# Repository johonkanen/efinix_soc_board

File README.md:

# efinix_soc_board

Linux-capable control card for an AC in/out lab power supply, based on the **Efinix Titanium Ti135N484I3** FPGA. The
FPGA's hardened quad-core RISC-V runs Linux, with 1 GB LPDDR4, Gigabit Ethernet and eMMC. The card plugs into the
power supply baseboard ([ac_psu_kicad](https://github.com/johonkanen/ac_psu_kicad)) in place of the earlier Ti60F225
and Agilex 5 cards.

Status: schematic in progress. See **[STATUS.md](STATUS.md)** for where the work stands and what comes next.

| | |
|---|---|
| [MIGRATION_PLAN.md](MIGRATION_PLAN.md) | plan and decisions |
| [TI135_PCB_NOTES.md](TI135_PCB_NOTES.md) | Ti135 PCB design rules (banks, sequencing, configuration, LPDDR4) |
| [MECHANICAL.md](MECHANICAL.md) | outline and baseboard connector positions |
| [POWER_BUDGET.md](POWER_BUDGET.md) | power estimate and regulators |

The KiCad 10 project in `kicad/` is generated by scripts (`tools/build_schematic.sh`), using
[proteus2kicad](https://github.com/johonkanen/proteus2kicad) as a submodule in `tools/p2k`.

## Board

<!-- board-plots:start -->
<!-- Generated by kicad-board-plots; edits between these markers are overwritten. -->

3D renders and copper layers of `kicad/ti135_card.kicad_pcb`, the layers in stack order without silkscreen. Plotted by [kicad-board-plots](https://github.com/johonkanen/kicad-board-plots) on each board change; the images live on the `renders` branch.

<table>
<tr>
<td align="center"><br><b>3D, top</b></td>
<td align="center"><br><b>3D, bottom (seen from below)</b></td>
</tr>
<tr>
<td align="center"><br><b>F.Cu: signal (top)</b></td>
<td align="center"><br><b>In1.Cu: GND plane</b></td>
</tr>
<tr>
<td align="center"><br><b>In2.Cu: signal, phy_avdd33 pour</b></td>
<td align="center"><br><b>In3.Cu: 1V1, VCORE, 3V3, GND planes</b></td>
</tr>
<tr>
<td align="center"><br><b>In4.Cu: 1V8, 0V85 planes</b></td>
<td align="center"><br><b>In5.Cu: signal</b></td>
</tr>
<tr>
<td align="center"><br><b>In6.Cu: GND plane</b></td>
<td align="center"><br><b>B.Cu: signal, 1V1, GND, Net-(U201-SW), 5V0, 1V8 and 9 more pours (bottom, seen from the top)</b></td>
</tr>
</table>

<!-- board-plots:end -->

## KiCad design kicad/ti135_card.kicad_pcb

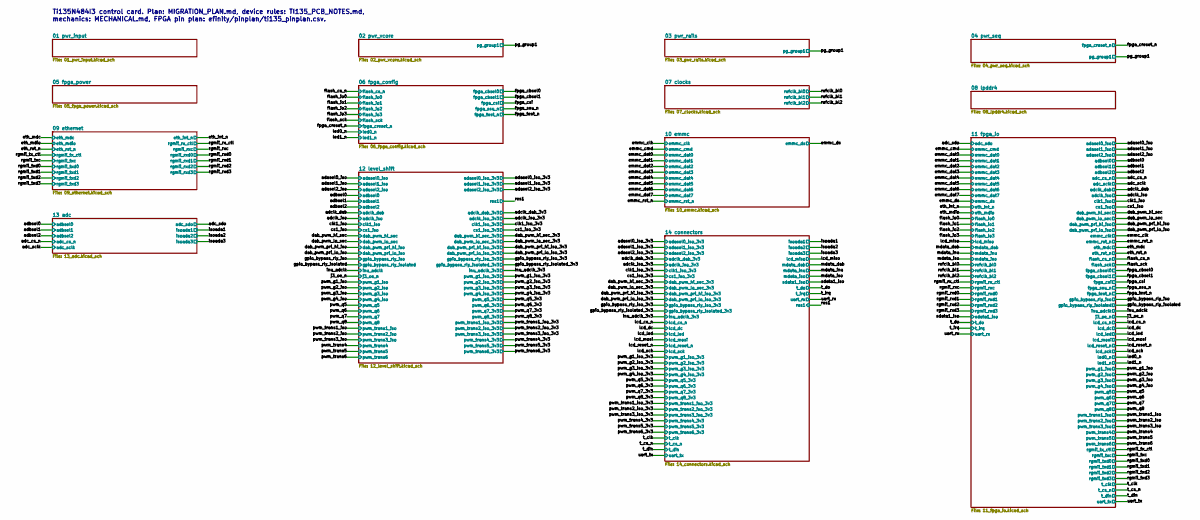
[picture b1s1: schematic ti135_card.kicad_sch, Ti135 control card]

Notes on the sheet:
Ti135N484I3 control card. Plan: MIGRATION_PLAN.md, device rules: TI135_PCB_NOTES.md, mechanics: MECHANICAL.md, FPGA pin plan: efinity/pinplan/ti135_pinplan.csv.

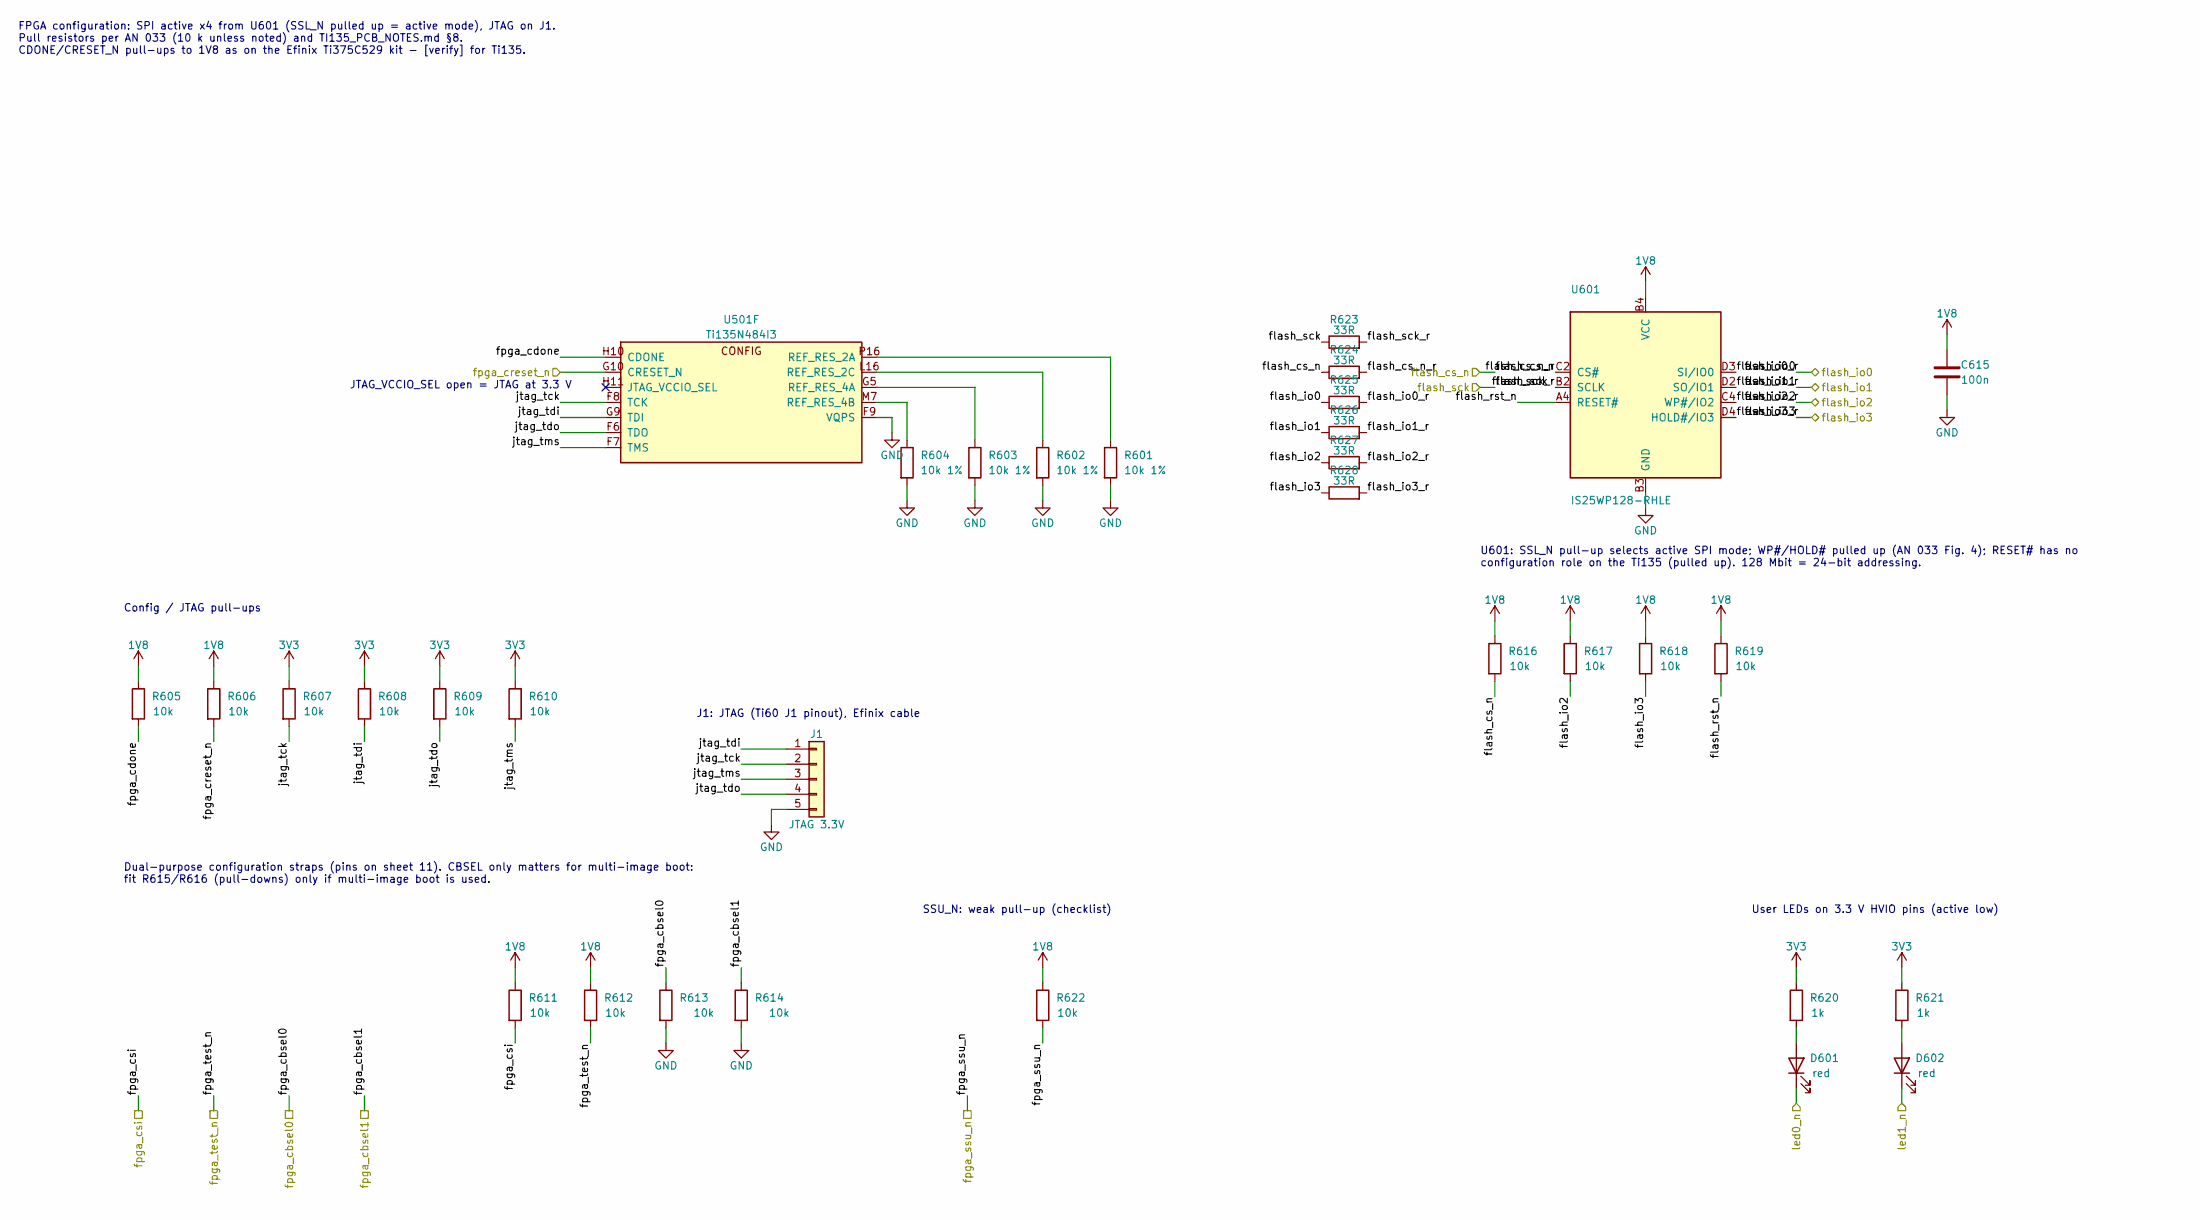
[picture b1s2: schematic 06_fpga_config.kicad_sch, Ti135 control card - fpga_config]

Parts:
C615: 100n; C_0201_0603Metric; LCSC C190183
D601, D602: red; LED_0603_1608Metric; LCSC C2286
J1: JTAG 3.3V; PinHeader_1x05_P2.54mm_Vertical; LCSC C492404
R601: 10k 1%; R_0201_0603Metric; LCSC C106225
R602, R603, R604: 10k 1%; R_0402_1005Metric; LCSC C25744
R605, R606, R607, R608, R609, R610, R611, R612, R613, R614, R616, R617, R618, R619, R622: 10k; R_0201_0603Metric; LCSC C473048
R620, R621: 1k; R_0402_1005Metric; LCSC C11702
R623, R624, R625, R626, R627, R628: 33R; R_0201_0603Metric; LCSC C320843
U501: Ti135N484I3; LFBGA-484_18x18mm_Layout22x22_P0.8mm
U601: IS25WP128-RHLE; MX25U25645G_CSP24_6x8mm_P1.0mm; LCSC C1349419

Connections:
1V8: C615.1, R605.1, R606.1, R611.1, R612.1, R616.1, R617.1, R618.1, R619.1, R622.1, U601.B4 (VCC); also elsewhere on the board
3V3: R607.1, R608.1, R609.1, R610.1, R620.1, R621.1; also elsewhere on the board
/06 fpga_config/flash_cs_n_r: R624.2, U601.C2 (CS#)
/06 fpga_config/flash_io0_r: R625.2, U601.D3 (SI/IO0)
/06 fpga_config/flash_io1_r: R626.2, U601.D2 (SO/IO1)
/06 fpga_config/flash_io2_r: R627.2, U601.C4 (WP#/IO2)
/06 fpga_config/flash_io3_r: R628.2, U601.D4 (HOLD#/IO3)
/06 fpga_config/flash_rst_n: R619.2, U601.A4 (RESET#)
/06 fpga_config/flash_sck_r: R623.2, U601.B2 (SCLK)
/06 fpga_config/fpga_cdone: R605.2, U501.H10 (CDONE)
/06 fpga_config/jtag_tck: J1.2, R607.2, U501.F8 (TCK)
/06 fpga_config/jtag_tdi: J1.1, R608.2, U501.G9 (TDI)
/06 fpga_config/jtag_tdo: J1.4, R609.2, U501.F6 (TDO)
/06 fpga_config/jtag_tms: J1.3, R610.2, U501.F7 (TMS)
/flash_cs_n: R616.2, R624.1; also elsewhere on the board
/flash_io0: R625.1; also elsewhere on the board
/flash_io1: R626.1; also elsewhere on the board
/flash_io2: R617.2, R627.1; also elsewhere on the board
/flash_io3: R618.2, R628.1; also elsewhere on the board
/flash_sck: R623.1; also elsewhere on the board
/fpga_cbsel0: R613.1; also elsewhere on the board
/fpga_cbsel1: R614.1; also elsewhere on the board
/fpga_creset_n: R606.2, U501.G10 (CRESET_N); also elsewhere on the board
/fpga_csi: R611.2; also elsewhere on the board
/fpga_ssu_n: R622.2; also elsewhere on the board
/fpga_test_n: R612.2; also elsewhere on the board
/led0_n: D601.1 (K); also elsewhere on the board
/led1_n: D602.1 (K); also elsewhere on the board
GND: C615.2, J1.5, R601.2, R602.2, R603.2, R604.2, R613.2, R614.2, U501.F9 (VQPS), U601.B3 (GND); also elsewhere on the board
unnamed: D601.2 (A), R620.2
unnamed: D602.2 (A), R621.2
unnamed: R601.1, U501.P16 (REF_RES_2A)
unnamed: R602.1, U501.L16 (REF_RES_2C)
unnamed: R603.1, U501.G5 (REF_RES_4A)
unnamed: R604.1, U501.M7 (REF_RES_4B)

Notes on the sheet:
Config / JTAG pull-ups
User LEDs on 3.3 V HVIO pins (active low)
JTAG_VCCIO_SEL open = JTAG at 3.3 V
SSU_N: weak pull-up (checklist)
U601: SSL_N pull-up selects active SPI mode; WP#/HOLD# pulled up (AN 033 Fig. 4); RESET# has no configuration role on the Ti135 (pulled up). 128 Mbit = 24-bit addressing.
J1: JTAG (Ti60 J1 pinout), Efinix cable
Dual-purpose configuration straps (pins on sheet 11). CBSEL only matters for multi-image boot: fit R615/R616 (pull-downs) only if multi-image boot is used.
FPGA configuration: SPI active x4 from U601 (SSL_N pulled up = active mode), JTAG on J1. Pull resistors per AN 033 (10 k unless noted) and TI135_PCB_NOTES.md §8. CDONE/CRESET_N pull-ups to 1V8 as on the Efinix Ti375C529 kit - [verify] for Ti135.

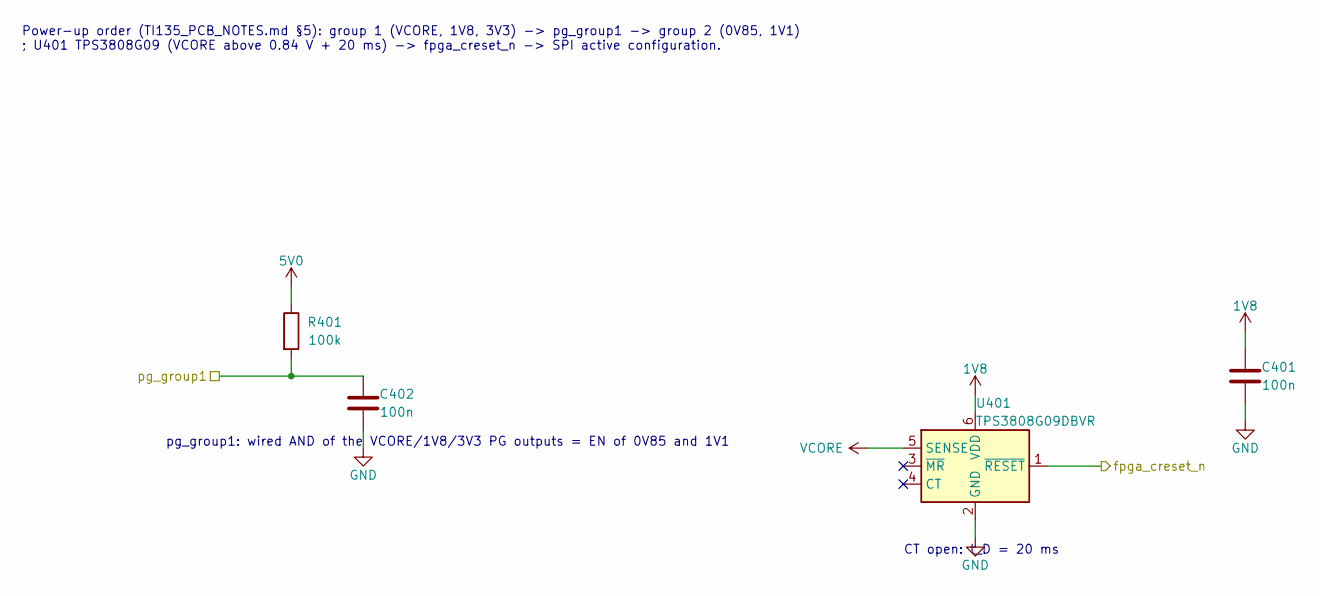
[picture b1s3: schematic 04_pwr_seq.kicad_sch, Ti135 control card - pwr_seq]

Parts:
C401, C402: 100n; C_0201_0603Metric; LCSC C190183
R401: 100k; R_0402_1005Metric; LCSC C25741
U401: TPS3808G09DBVR; SOT-23-6; LCSC C24584

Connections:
1V8: C401.1, U401.6 (VDD); also elsewhere on the board
5V0: R401.1; also elsewhere on the board
/fpga_creset_n: U401.1 (~RESET); also elsewhere on the board
/pg_group1: C402.1, R401.2; also elsewhere on the board
GND: C401.2, C402.2, U401.2 (GND); also elsewhere on the board
VCORE: U401.5 (SENSE); also elsewhere on the board

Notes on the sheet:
CT open: t_D = 20 ms
pg_group1: wired AND of the VCORE/1V8/3V3 PG outputs = EN of 0V85 and 1V1
Power-up order (TI135_PCB_NOTES.md §5): group 1 (VCORE, 1V8, 3V3) -> pg_group1 -> group 2 (0V85, 1V1) ; U401 TPS3808G09 (VCORE above 0.84 V + 20 ms) -> fpga_creset_n -> SPI active configuration.

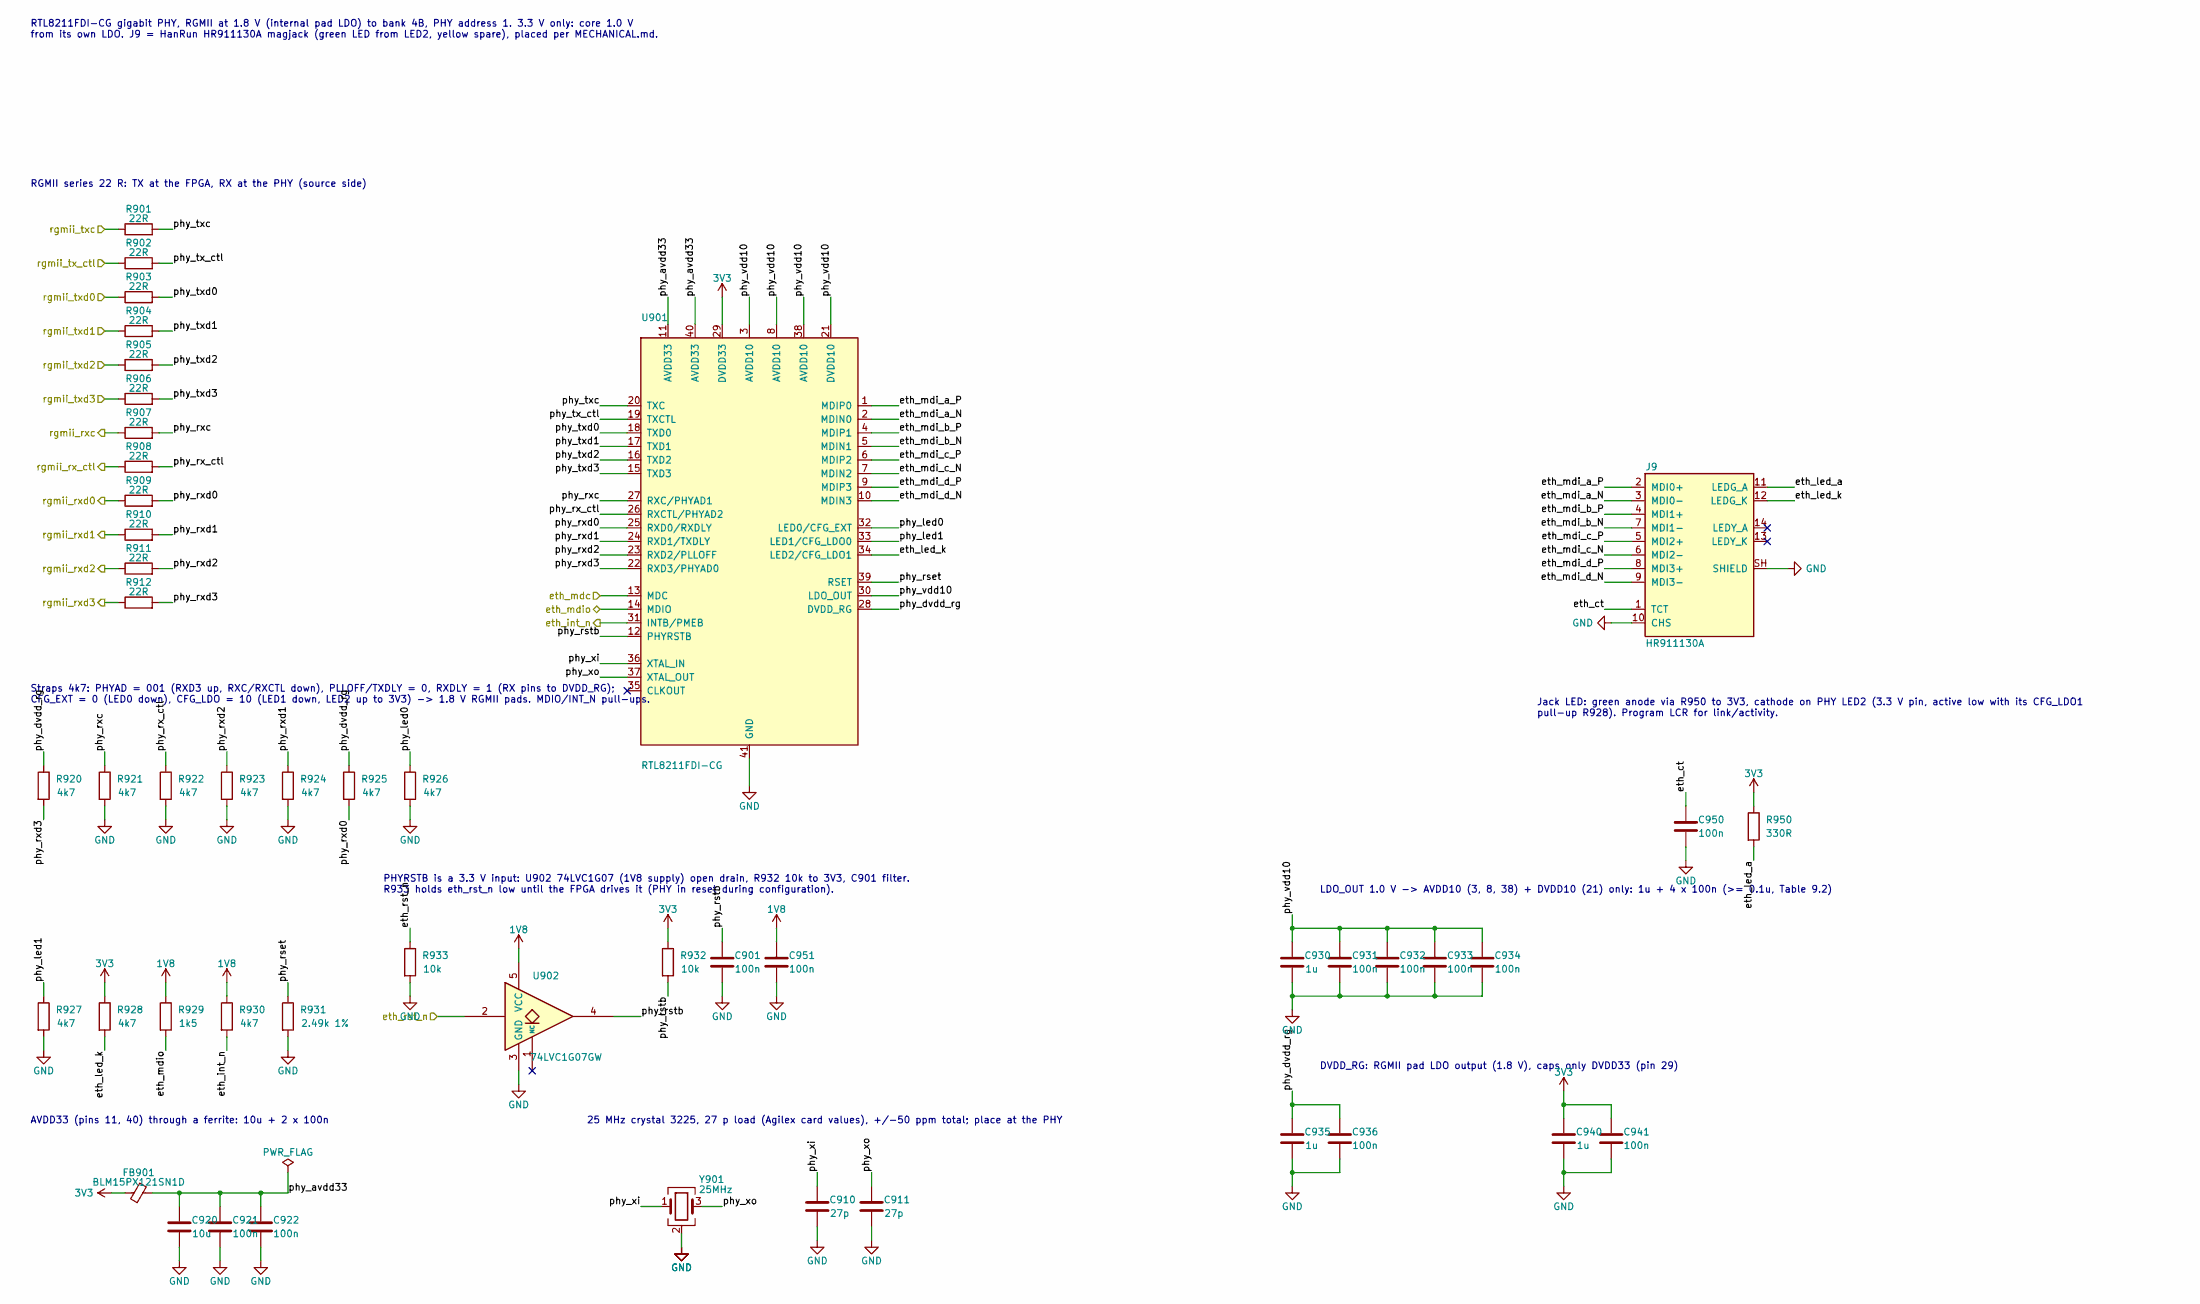
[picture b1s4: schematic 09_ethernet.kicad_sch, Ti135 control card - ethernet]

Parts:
C901, C950: 100n; C_0402_1005Metric; LCSC C1525
C910, C911: 27p; C_0402_1005Metric; LCSC C1557
C920: 10u; C_0805_2012Metric; LCSC C15850
C921, C922, C931, C932, C933, C934, C936, C941, C951: 100n; C_0201_0603Metric; LCSC C190183
C930, C935, C940: 1u; C_0201_0603Metric; LCSC C272877
FB901: BLM15PX121SN1D; L_0402_1005Metric; LCSC C88970
J9: HR911130A; RJ45_Hanrun_HR911130A_Horizontal; LCSC C54408
R901, R902, R903, R904, R905, R906: 22R; R_0402_1005Metric; LCSC C25092
R907, R908, R909, R910, R911, R912: 22R; R_0201_0603Metric; LCSC C155743
R920, R921, R922, R923, R924, R925: 4k7; R_0201_0603Metric; LCSC C270346
R926, R927, R928, R930: 4k7; R_0402_1005Metric; LCSC C25900
R929: 1k5; R_0402_1005Metric; LCSC C25867
R931: 2.49k 1%; R_0402_1005Metric; LCSC C25884
R932, R933: 10k; R_0402_1005Metric; LCSC C25744
R950: 330R; R_0402_1005Metric; LCSC C25104
U901: RTL8211FDI-CG; QFN-40-1EP_5x5mm_P0.4mm_EP3.6x3.6mm_ThermalVias; LCSC C692886
U902: 74LVC1G07GW; SOT-353_SC-70-5; LCSC C282345
Y901: 25MHz; Crystal_SMD_3225-4Pin_3.2x2.5mm; LCSC C70593

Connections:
1V8: C951.1, R929.1, R930.1, U902.5 (VCC); also elsewhere on the board
3V3: C940.1, C941.1, FB901.1, R928.1, R932.1, R950.1, U901.29 (DVDD33); also elsewhere on the board
/09 ethernet/eth_ct: C950.1, J9.1 (TCT)
/09 ethernet/eth_led_a: J9.11 (LEDG_A), R950.2
/09 ethernet/eth_led_k: J9.12 (LEDG_K), R928.2, U901.34 (LED2/CFG_LDO1)
/09 ethernet/eth_mdi_a_N: J9.3 (MDI0-), U901.2 (MDIN0)
/09 ethernet/eth_mdi_a_P: J9.2 (MDI0+), U901.1 (MDIP0)
/09 ethernet/eth_mdi_b_N: J9.7 (MDI1-), U901.5 (MDIN1)
/09 ethernet/eth_mdi_b_P: J9.4 (MDI1+), U901.4 (MDIP1)
/09 ethernet/eth_mdi_c_N: J9.6 (MDI2-), U901.7 (MDIN2)
/09 ethernet/eth_mdi_c_P: J9.5 (MDI2+), U901.6 (MDIP2)
/09 ethernet/eth_mdi_d_N: J9.9 (MDI3-), U901.10 (MDIN3)
/09 ethernet/eth_mdi_d_P: J9.8 (MDI3+), U901.9 (MDIP3)
/09 ethernet/phy_avdd33: C920.1, C921.1, C922.1, FB901.2, U901.11 (AVDD33), U901.40 (AVDD33)
/09 ethernet/phy_dvdd_rg: C935.1, C936.1, R920.1, R925.1, U901.28 (DVDD_RG)
/09 ethernet/phy_led0: R926.1, U901.32 (LED0/CFG_EXT)
/09 ethernet/phy_led1: R927.1, U901.33 (LED1/CFG_LDO0)
/09 ethernet/phy_rset: R931.1, U901.39 (RSET)
/09 ethernet/phy_rstb: C901.1, R932.2, U901.12 (PHYRSTB), U902.4
/09 ethernet/phy_rx_ctl: R908.2, R922.1, U901.26 (RXCTL/PHYAD2)
/09 ethernet/phy_rxc: R907.2, R921.1, U901.27 (RXC/PHYAD1)
/09 ethernet/phy_rxd0: R909.2, R925.2, U901.25 (RXD0/RXDLY)
/09 ethernet/phy_rxd1: R910.2, R924.1, U901.24 (RXD1/TXDLY)
/09 ethernet/phy_rxd2: R911.2, R923.1, U901.23 (RXD2/PLLOFF)
/09 ethernet/phy_rxd3: R912.2, R920.2, U901.22 (RXD3/PHYAD0)
/09 ethernet/phy_tx_ctl: R902.2, U901.19 (TXCTL)
/09 ethernet/phy_txc: R901.2, U901.20 (TXC)
/09 ethernet/phy_txd0: R903.2, U901.18 (TXD0)
/09 ethernet/phy_txd1: R904.2, U901.17 (TXD1)
/09 ethernet/phy_txd2: R905.2, U901.16 (TXD2)
/09 ethernet/phy_txd3: R906.2, U901.15 (TXD3)
/09 ethernet/phy_vdd10: C930.1, C931.1, C932.1, C933.1, C934.1, U901.3 (AVDD10), U901.8 (AVDD10), U901.21 (DVDD10), U901.30 (LDO_OUT), U901.38 (AVDD10)
/09 ethernet/phy_xi: C910.1, U901.36 (XTAL_IN), Y901.1
/09 ethernet/phy_xo: C911.1, U901.37 (XTAL_OUT), Y901.3
/eth_int_n: R930.2, U901.31 (INTB/PMEB); also elsewhere on the board
/eth_mdc: U901.13 (MDC); also elsewhere on the board
/eth_mdio: R929.2, U901.14 (MDIO); also elsewhere on the board
/eth_rst_n: R933.1, U902.2; also elsewhere on the board
/rgmii_rx_ctl: R908.1; also elsewhere on the board
/rgmii_rxc: R907.1; also elsewhere on the board
/rgmii_rxd0: R909.1; also elsewhere on the board
/rgmii_rxd1: R910.1; also elsewhere on the board
/rgmii_rxd2: R911.1; also elsewhere on the board
/rgmii_rxd3: R912.1; also elsewhere on the board
/rgmii_tx_ctl: R902.1; also elsewhere on the board
/rgmii_txc: R901.1; also elsewhere on the board
/rgmii_txd0: R903.1; also elsewhere on the board
/rgmii_txd1: R904.1; also elsewhere on the board
/rgmii_txd2: R905.1; also elsewhere on the board
/rgmii_txd3: R906.1; also elsewhere on the board
GND: C901.2, C910.2, C911.2, C920.2, C921.2, C922.2, C930.2, C931.2, C932.2, C933.2, C934.2, C935.2, C936.2, C940.2, C941.2, C950.2, C951.2, J9.10 (CHS), J9.SH (SHIELD), R921.2, R922.2, R923.2, R924.2, R926.2, R927.2, R931.2, R933.2, U901.41 (GND), U902.3 (GND), Y901.2 (G), Y901.4 (G); also elsewhere on the board

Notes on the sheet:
RGMII series 22 R: TX at the FPGA, RX at the PHY (source side)
LDO_OUT 1.0 V -> AVDD10 (3, 8, 38) + DVDD10 (21) only: 1u + 4 x 100n (>= 0.1u, Table 9.2)
PHYRSTB is a 3.3 V input: U902 74LVC1G07 (1V8 supply) open drain, R932 10k to 3V3, C901 filter. R933 holds eth_rst_n low until the FPGA drives it (PHY in reset during configuration).
DVDD_RG: RGMII pad LDO output (1.8 V), caps only
Jack LED: green anode via R950 to 3V3, cathode on PHY LED2 (3.3 V pin, active low with its CFG_LDO1 pull-up R928). Program LCR for link/activity.
Straps 4k7: PHYAD = 001 (RXD3 up, RXC/RXCTL down), PLLOFF/TXDLY = 0, RXDLY = 1 (RX pins to DVDD_RG); CFG_EXT = 0 (LED0 down), CFG_LDO = 10 (LED1 down, LED2 up to 3V3) -> 1.8 V RGMII pads. MDIO/INT_N pull-ups.
25 MHz crystal 3225, 27 p load (Agilex card values), +/-50 ppm total; place at the PHY
RTL8211FDI-CG gigabit PHY, RGMII at 1.8 V (internal pad LDO) to bank 4B, PHY address 1. 3.3 V only: core 1.0 V from its own LDO. J9 = HanRun HR911130A magjack (green LED from LED2, yellow spare), placed per MECHANICAL.md.
DVDD33 (pin 29)
AVDD33 (pins 11, 40) through a ferrite: 10u + 2 x 100n

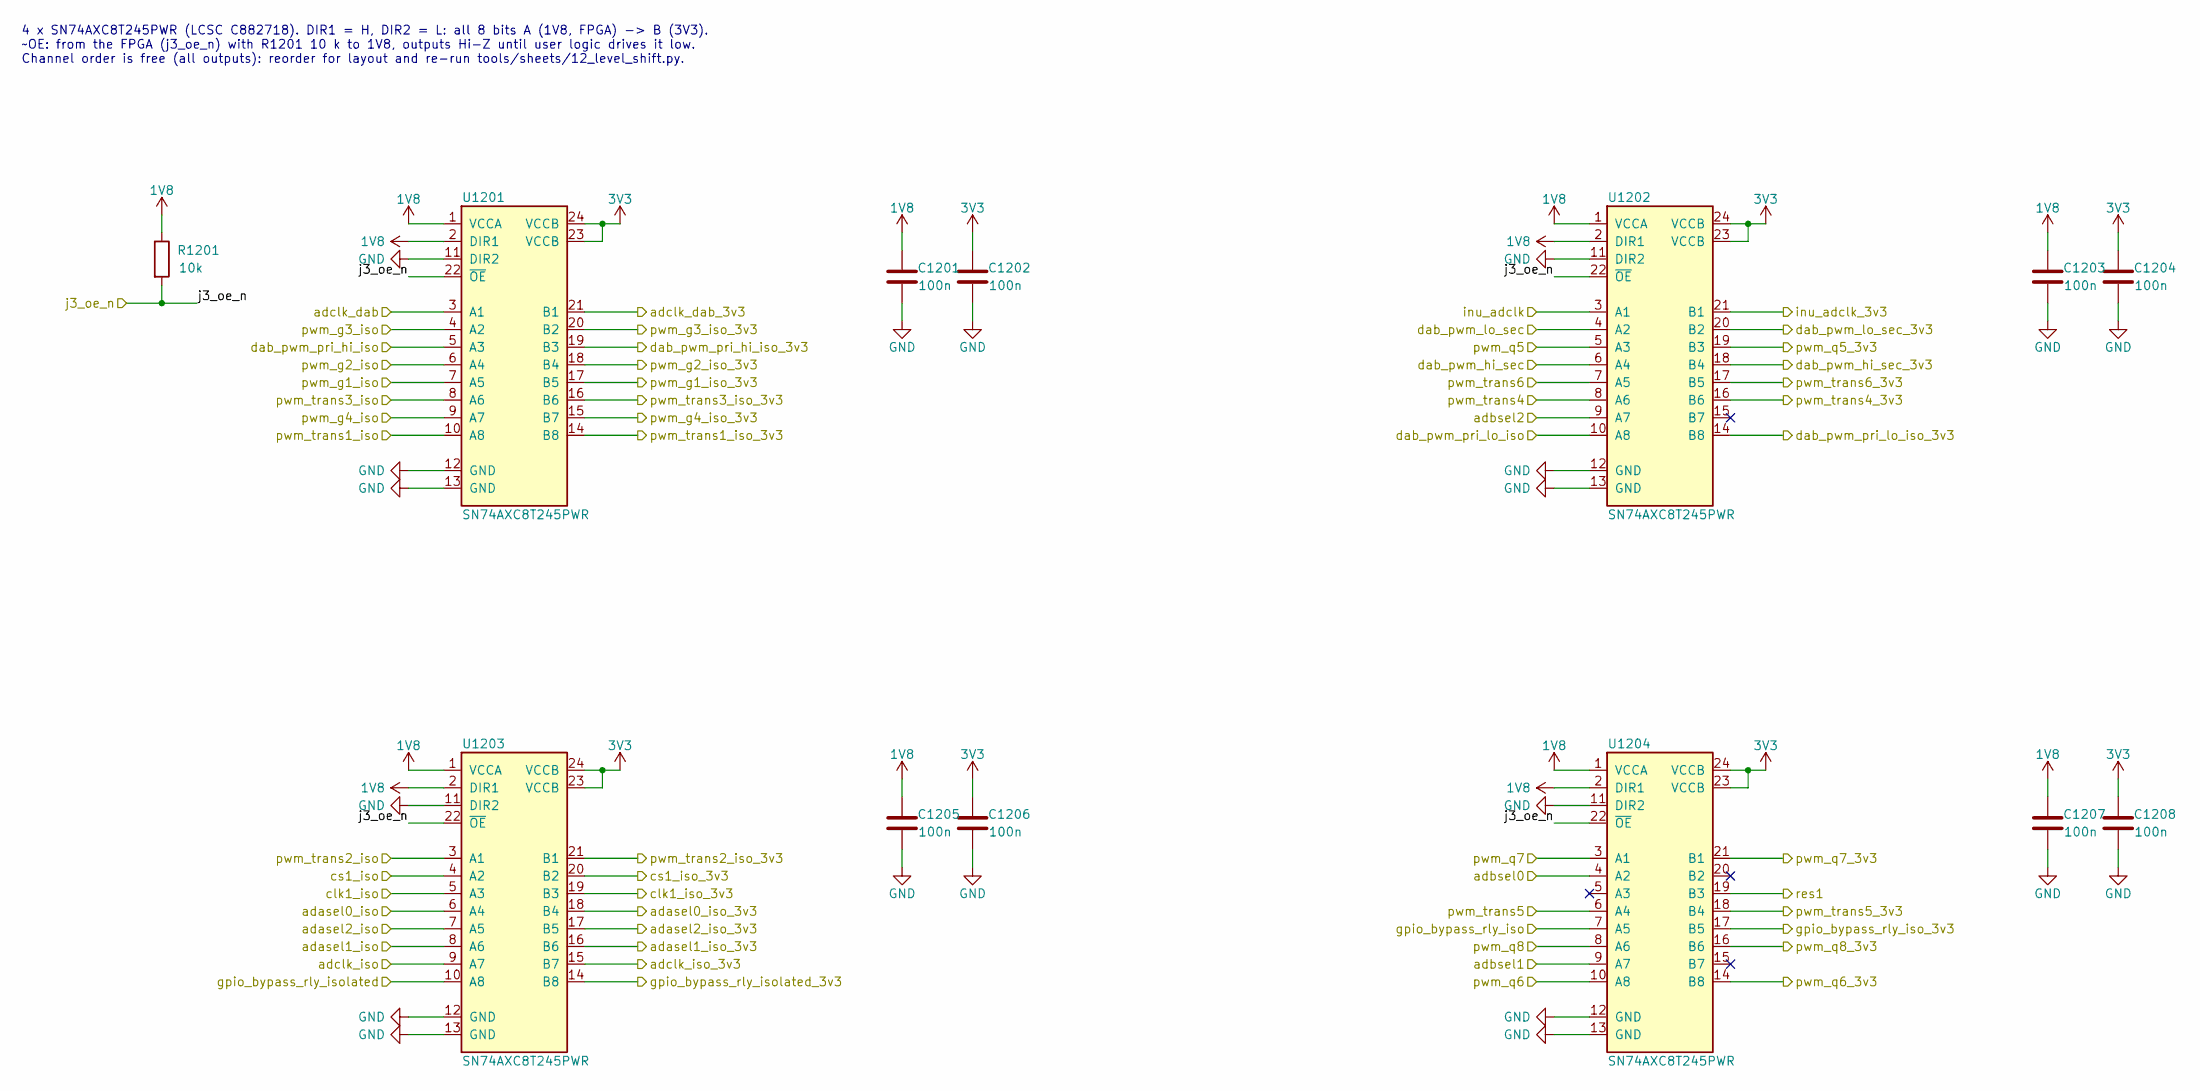
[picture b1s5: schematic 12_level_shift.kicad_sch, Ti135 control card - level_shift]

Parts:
C1201, C1202, C1203, C1204, C1205, C1206, C1207, C1208: 100n; C_0201_0603Metric; LCSC C190183
R1201: 10k; R_0402_1005Metric; LCSC C25744
U1201, U1202, U1203, U1204: SN74AXC8T245PWR; TSSOP-24_4.4x7.8mm_P0.65mm; LCSC C882718

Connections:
1V8: C1201.1, C1203.1, C1205.1, C1207.1, R1201.1, U1201.1 (VCCA), U1201.2 (DIR1), U1202.1 (VCCA), U1202.2 (DIR1), U1203.1 (VCCA), U1203.2 (DIR1), U1204.1 (VCCA), U1204.2 (DIR1); also elsewhere on the board
3V3: C1202.1, C1204.1, C1206.1, C1208.1, U1201.23 (VCCB), U1201.24 (VCCB), U1202.23 (VCCB), U1202.24 (VCCB), U1203.23 (VCCB), U1203.24 (VCCB), U1204.23 (VCCB), U1204.24 (VCCB); also elsewhere on the board
/adasel0_iso: U1203.6 (A4); also elsewhere on the board
/adasel0_iso_3v3: U1203.18 (B4); also elsewhere on the board
/adasel1_iso: U1203.8 (A6); also elsewhere on the board
/adasel1_iso_3v3: U1203.16 (B6); also elsewhere on the board
/adasel2_iso: U1203.7 (A5); also elsewhere on the board
/adasel2_iso_3v3: U1203.17 (B5); also elsewhere on the board
/adbsel0: U1204.4 (A2); also elsewhere on the board
/adbsel1: U1204.9 (A7); also elsewhere on the board
/adbsel2: U1202.9 (A7); also elsewhere on the board
/adclk_dab: U1201.3 (A1); also elsewhere on the board
/adclk_dab_3v3: U1201.21 (B1); also elsewhere on the board
/adclk_iso: U1203.9 (A7); also elsewhere on the board
/adclk_iso_3v3: U1203.15 (B7); also elsewhere on the board
/clk1_iso: U1203.5 (A3); also elsewhere on the board
/clk1_iso_3v3: U1203.19 (B3); also elsewhere on the board
/cs1_iso: U1203.4 (A2); also elsewhere on the board
/cs1_iso_3v3: U1203.20 (B2); also elsewhere on the board
/dab_pwm_hi_sec: U1202.6 (A4); also elsewhere on the board
/dab_pwm_hi_sec_3v3: U1202.18 (B4); also elsewhere on the board
/dab_pwm_lo_sec: U1202.4 (A2); also elsewhere on the board
/dab_pwm_lo_sec_3v3: U1202.20 (B2); also elsewhere on the board
/dab_pwm_pri_hi_iso: U1201.5 (A3); also elsewhere on the board
/dab_pwm_pri_hi_iso_3v3: U1201.19 (B3); also elsewhere on the board
/dab_pwm_pri_lo_iso: U1202.10 (A8); also elsewhere on the board
/dab_pwm_pri_lo_iso_3v3: U1202.14 (B8); also elsewhere on the board
/gpio_bypass_rly_iso: U1204.7 (A5); also elsewhere on the board
/gpio_bypass_rly_iso_3v3: U1204.17 (B5); also elsewhere on the board
/gpio_bypass_rly_isolated: U1203.10 (A8); also elsewhere on the board
/gpio_bypass_rly_isolated_3v3: U1203.14 (B8); also elsewhere on the board
/inu_adclk: U1202.3 (A1); also elsewhere on the board
/inu_adclk_3v3: U1202.21 (B1); also elsewhere on the board
/j3_oe_n: R1201.2, U1201.22 (~OE), U1202.22 (~OE), U1203.22 (~OE), U1204.22 (~OE); also elsewhere on the board
/pwm_g1_iso: U1201.7 (A5); also elsewhere on the board
/pwm_g1_iso_3v3: U1201.17 (B5); also elsewhere on the board
/pwm_g2_iso: U1201.6 (A4); also elsewhere on the board
/pwm_g2_iso_3v3: U1201.18 (B4); also elsewhere on the board
/pwm_g3_iso: U1201.4 (A2); also elsewhere on the board
/pwm_g3_iso_3v3: U1201.20 (B2); also elsewhere on the board
/pwm_g4_iso: U1201.9 (A7); also elsewhere on the board
/pwm_g4_iso_3v3: U1201.15 (B7); also elsewhere on the board
/pwm_q5: U1202.5 (A3); also elsewhere on the board
/pwm_q5_3v3: U1202.19 (B3); also elsewhere on the board
/pwm_q6: U1204.10 (A8); also elsewhere on the board
/pwm_q6_3v3: U1204.14 (B8); also elsewhere on the board
/pwm_q7: U1204.3 (A1); also elsewhere on the board
/pwm_q7_3v3: U1204.21 (B1); also elsewhere on the board
/pwm_q8: U1204.8 (A6); also elsewhere on the board
/pwm_q8_3v3: U1204.16 (B6); also elsewhere on the board
/pwm_trans1_iso: U1201.10 (A8); also elsewhere on the board
/pwm_trans1_iso_3v3: U1201.14 (B8); also elsewhere on the board
/pwm_trans2_iso: U1203.3 (A1); also elsewhere on the board
/pwm_trans2_iso_3v3: U1203.21 (B1); also elsewhere on the board
/pwm_trans3_iso: U1201.8 (A6); also elsewhere on the board
/pwm_trans3_iso_3v3: U1201.16 (B6); also elsewhere on the board
/pwm_trans4: U1202.8 (A6); also elsewhere on the board
/pwm_trans4_3v3: U1202.16 (B6); also elsewhere on the board
/pwm_trans5: U1204.6 (A4); also elsewhere on the board
/pwm_trans5_3v3: U1204.18 (B4); also elsewhere on the board
/pwm_trans6: U1202.7 (A5); also elsewhere on the board
/pwm_trans6_3v3: U1202.17 (B5); also elsewhere on the board
/res1: U1204.19 (B3); also elsewhere on the board
GND: C1201.2, C1202.2, C1203.2, C1204.2, C1205.2, C1206.2, C1207.2, C1208.2, U1201.11 (DIR2), U1201.12 (GND), U1201.13 (GND), U1202.11 (DIR2), U1202.12 (GND), U1202.13 (GND), U1203.11 (DIR2), U1203.12 (GND), U1203.13 (GND), U1204.11 (DIR2), U1204.12 (GND), U1204.13 (GND); also elsewhere on the board

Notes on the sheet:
4 x SN74AXC8T245PWR (LCSC C882718). DIR1 = H, DIR2 = L: all 8 bits A (1V8, FPGA) -> B (3V3). ~OE: from the FPGA (j3_oe_n) with R1201 10 k to 1V8, outputs Hi-Z until user logic drives it low. Channel order is free (all outputs): reorder for layout and re-run tools/sheets/12_level_shift.py.
